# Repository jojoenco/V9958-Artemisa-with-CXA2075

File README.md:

# V9958-Artemisa-MSX-with-CXA2075
Video extension Artemisa MSX V9958 with CXA2075 (Composiet)

V9958 for Artemisa(Made By Alvaro Polo) [Artemisa MSX Project](https://github.com/apoloval/artemisa)

I made an Video Extension for the Artemisa with an V9958 and en CXA2075(for Composiet out).
Which works fine in MSX1 modus, however I also want it to work with MSX2 Modus (screen4 to 8).
Have tried a cartridge with a lot of rom's for V9958 and an MSX2 Rom's on the mainboard, but that did not work out.

For R12 you have to use a Resistor exacly 85.5 Ohm, I ordered a few but after a few mistakes I had none, 
so measured 82 Ohm resistors until I found 82,5 Ohm, and works fine.
The 2K61 I could not find measured so used exact version.

I did not test de S-video and de VGA.
And the Composiet picture has a litte noise.

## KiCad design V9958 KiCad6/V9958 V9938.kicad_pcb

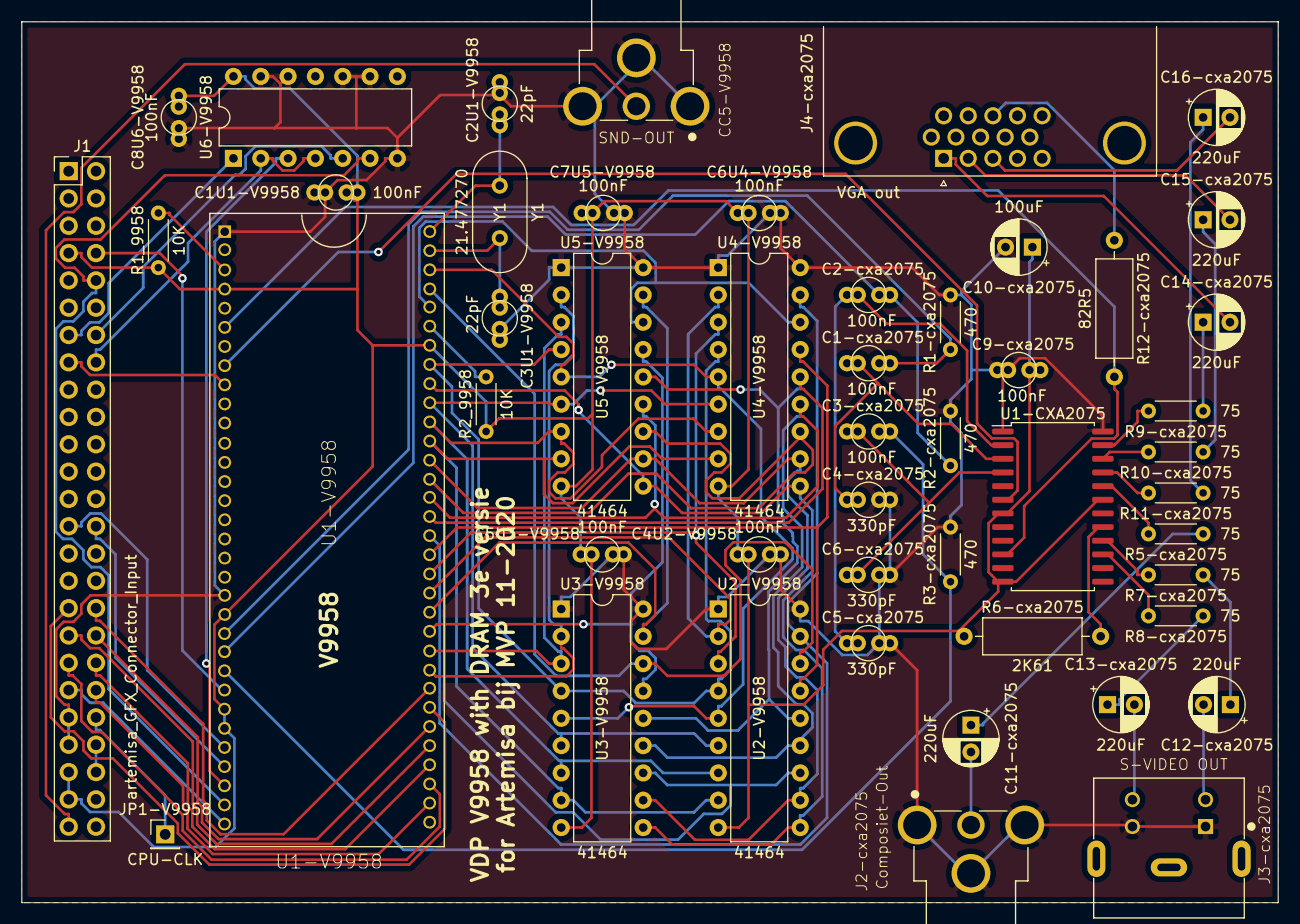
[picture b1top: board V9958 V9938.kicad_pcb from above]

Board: 2 copper layers, 116.8 x 81.9 mm, 49 parts (0 on the bottom side), 74 nets.

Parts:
C1-cxa2075, C1U1-V9958, C2-cxa2075, C3-cxa2075, C4U2-V9958, C5U3-V9958, C6U4-V9958, C7U5-V9958, C8U6-V9958, C9-cxa2075: 100nF; C_dual_hole_radial
C2U1-V9958, C3U1-V9958: 22pF; C_dual_hole_radial
C4-cxa2075, C5-cxa2075, C6-cxa2075: 330pF; C_dual_hole_radial
C10-cxa2075: 100uF; CP_Radial_D5.0mm_P2.50mm
C11-cxa2075, C12-cxa2075, C13-cxa2075, C14-cxa2075, C15-cxa2075, C16-cxa2075: 220uF; CP_Radial_D5.0mm_P2.50mm
CC5-V9958: SND-OUT; CUI_RCJ-013
J1: artemisa_GFX_Connector_Input; PinHeader_2x25_P2.54mm_Vertical
J2-cxa2075: Composiet-Out; CUI_RCJ-013
J3-cxa2075: S-VIDEO OUT; CUI_MD-40SM
J4-cxa2075: VGA out; DSUB-15-HD_Female_Horizontal_P2.29x1.98mm_EdgePinOffset8.35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
JP1-V9958: CPU-CLK; PinHeader_1x01_P2.54mm_Vertical
R1-cxa2075, R2-cxa2075, R3-cxa2075: 470; R_Axial_DIN0204_L3.6mm_D1.6mm_P5.08mm_Horizontal
R1_9958, R2_9958: 10K; R_Axial_DIN0204_L3.6mm_D1.6mm_P5.08mm_Horizontal
R5-cxa2075, R7-cxa2075, R8-cxa2075, R9-cxa2075, R10-cxa2075, R11-cxa2075: 75; R_Axial_DIN0204_L3.6mm_D1.6mm_P5.08mm_Horizontal
R6-cxa2075: 2K61; R_Axial_DIN0309_L9.0mm_D3.2mm_P12.70mm_Horizontal
R12-cxa2075: 82R5; R_Axial_DIN0309_L9.0mm_D3.2mm_P12.70mm_Horizontal
U1-CXA2075: CXA2075; SOP-24_7.5x15.4mm_P1.27mm
U1-V9958: V9958; DIP64-S
U2-V9958, U3-V9958, U4-V9958, U5-V9958: 41464; DIP-18_W7.62mm
U6-V9958: 74LS32; DIP-14_W7.62mm
Y1: 21.477270; Crystal_HC49-U_Vertical

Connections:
1<->cxa2075: C1U1-V9958.1, C4U2-V9958.1, C5U3-V9958.1, C6U4-V9958.1, C7U5-V9958.1, C8U6-V9958.1, C9-cxa2075.2, C10-cxa2075.1, J1.7, J1.45, J1.47, R1_9958.1, R2_9958.1, R6-cxa2075.1, U1-CXA2075.7, U1-CXA2075.12, U1-CXA2075.19, U1-V9958.4, U1-V9958.21, U1-V9958.26, U1-V9958.27, U1-V9958.58, U2-V9958.9, U3-V9958.9, U4-V9958.9, U5-V9958.9, U6-V9958.14
2<->cxa2075: C1-cxa2075.2, R1-cxa2075.1, U1-V9958.22
3<->cxa2075: C2-cxa2075.2, R2-cxa2075.1, U1-V9958.23
4<->cxa2075: C3-cxa2075.2, R3-cxa2075.1, U1-V9958.24
6<->cxa2075: R12-cxa2075.2, U1-CXA2075.10, U1-V9958.6
7<->cxa2075: C1U1-V9958.2, C2U1-V9958.1, C3U1-V9958.1, C4-cxa2075.2, C4U2-V9958.2, C5-cxa2075.2, C5U3-V9958.2, C6-cxa2075.2, C6U4-V9958.2, C7U5-V9958.2, C8U6-V9958.2, C9-cxa2075.1, C10-cxa2075.2, CC5-V9958.2, J1.41, J1.43, J2-cxa2075.2, J3-cxa2075.1, J3-cxa2075.2, R1-cxa2075.2, R2-cxa2075.2, R3-cxa2075.2, U1-CXA2075.1, U1-CXA2075.24, U1-V9958.1, U1-V9958.20, U2-V9958.1, U2-V9958.18, U3-V9958.1, U3-V9958.18, U4-V9958.1, U4-V9958.18, U5-V9958.1, U5-V9958.18, U6-V9958.7, U6-V9958.9, U6-V9958.10, U6-V9958.12, U6-V9958.13
8<->cxa2075: U1-CXA2075.6, U1-V9958.8
A0: U1-V9958.49, U2-V9958.14, U3-V9958.14, U4-V9958.14, U5-V9958.14
A1: U1-V9958.50, U2-V9958.13, U3-V9958.13, U4-V9958.13, U5-V9958.13
A2: U1-V9958.51, U2-V9958.12, U3-V9958.12, U4-V9958.12, U5-V9958.12
A3: U1-V9958.52, U2-V9958.11, U3-V9958.11, U4-V9958.11, U5-V9958.11
A4: U1-V9958.53, U2-V9958.8, U3-V9958.8, U4-V9958.8, U5-V9958.8
A5: U1-V9958.54, U2-V9958.7, U3-V9958.7, U4-V9958.7, U5-V9958.7
A6: U1-V9958.55, U2-V9958.6, U3-V9958.6, U4-V9958.6, U5-V9958.6
A7: U1-V9958.56, U2-V9958.10, U3-V9958.10, U4-V9958.10, U5-V9958.10
CD0: J1.34, U1-V9958.40
CD1: J1.33, U1-V9958.39
CD2: J1.36, U1-V9958.38
CD3: J1.35, U1-V9958.37
CD4: J1.38, U1-V9958.36
CD5: J1.37, U1-V9958.35
CD6: J1.40, U1-V9958.34
CD7: J1.39, U1-V9958.32
D0: U1-V9958.41, U3-V9958.2, U5-V9958.2
D1: U1-V9958.42, U3-V9958.3, U5-V9958.3
D2: U1-V9958.43, U3-V9958.15, U5-V9958.15
D3: U1-V9958.44, U3-V9958.17, U5-V9958.17
D4: U1-V9958.45, U2-V9958.2, U4-V9958.2
D5: U1-V9958.46, U2-V9958.3, U4-V9958.3
D6: U1-V9958.47, U2-V9958.15, U4-V9958.15
D7: U1-V9958.48, U2-V9958.17, U4-V9958.17
M0: J1.28, U1-V9958.29
M1: J1.27, U1-V9958.28
unnamed: C1-cxa2075.1, C4-cxa2075.1, U1-CXA2075.3
unnamed: C2-cxa2075.1, C5-cxa2075.1, U1-CXA2075.2
unnamed: C2U1-V9958.2, U1-V9958.64, Y1.1
unnamed: C3-cxa2075.1, C6-cxa2075.1, U1-CXA2075.4
unnamed: C3U1-V9958.2, U1-V9958.63, Y1.2
unnamed: C11-cxa2075.1, R5-cxa2075.1
unnamed: C11-cxa2075.2, J2-cxa2075.1
unnamed: C12-cxa2075.1, R7-cxa2075.1
unnamed: C12-cxa2075.2, J3-cxa2075.3
unnamed: C13-cxa2075.1, R8-cxa2075.1
unnamed: C13-cxa2075.2, J3-cxa2075.4
unnamed: C14-cxa2075.1, R9-cxa2075.1
unnamed: C14-cxa2075.2, J4-cxa2075.1
unnamed: C15-cxa2075.1, R10-cxa2075.1
unnamed: C15-cxa2075.2, J4-cxa2075.2
unnamed: C16-cxa2075.1, R11-cxa2075.1
unnamed: C16-cxa2075.2, J4-cxa2075.3
unnamed: CC5-V9958.1, J1.49
unnamed: J1.8, U1-V9958.25
unnamed: J1.10, U1-V9958.31, U6-V9958.6
unnamed: J1.13, U6-V9958.1
unnamed: J1.14, U6-V9958.5
unnamed: J1.15, U1-V9958.9
unnamed: J1.16, U6-V9958.2, U6-V9958.4
unnamed: J1.42, JP1-V9958.1
unnamed: J1.44, J1.46
unnamed: J4-cxa2075.13, R12-cxa2075.1
unnamed: R1_9958.2, U1-V9958.3
unnamed: R2_9958.2, U1-V9958.59
unnamed: R5-cxa2075.2, U1-CXA2075.20
unnamed: R6-cxa2075.2, U1-CXA2075.17
unnamed: R7-cxa2075.2, U1-CXA2075.16
unnamed: R8-cxa2075.2, U1-CXA2075.15
unnamed: R9-cxa2075.2, U1-CXA2075.23
unnamed: R10-cxa2075.2, U1-CXA2075.22
unnamed: R11-cxa2075.2, U1-CXA2075.21
unnamed: U1-V9958.30, U6-V9958.3
R_W: U1-V9958.57, U2-V9958.4, U3-V9958.4, U4-V9958.4, U5-V9958.4
~CAS_0: U1-V9958.61, U2-V9958.16, U3-V9958.16
~CAS_1: U1-V9958.60, U4-V9958.16, U5-V9958.16
~RAS: U1-V9958.62, U2-V9958.5, U3-V9958.5, U4-V9958.5, U5-V9958.5

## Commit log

2022-05-15 Create LICENSE
